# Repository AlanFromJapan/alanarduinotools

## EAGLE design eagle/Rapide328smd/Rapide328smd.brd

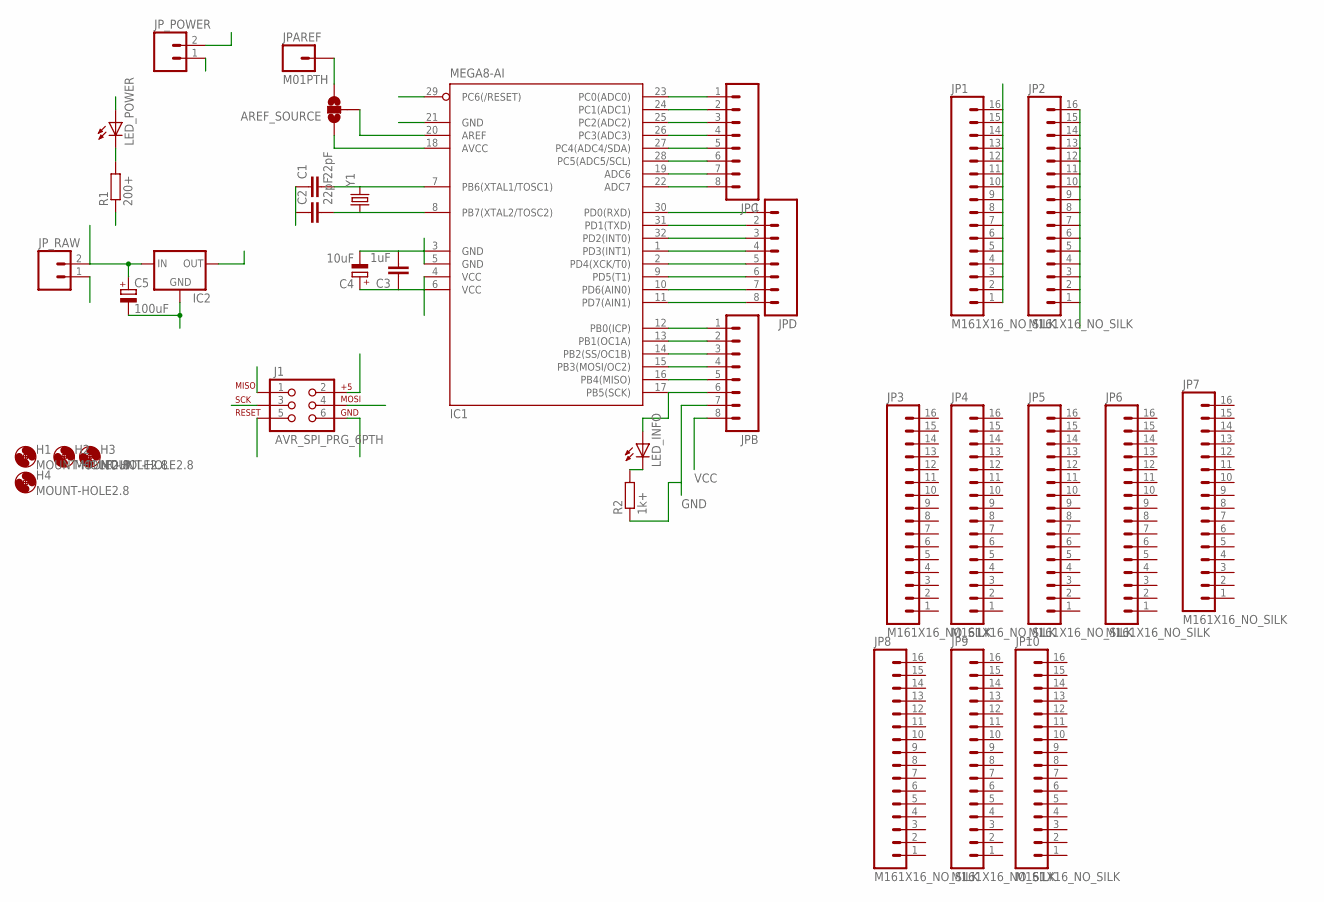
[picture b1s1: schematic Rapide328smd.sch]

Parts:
AREF_SOURCE: SOLDERJUMPER_2WAYPASTE1&2; SJ_3_PASTE1&2
C1, C2: 22pF; C025-024X044
C3: 1uF; C025-024X044
C4: 10uF; E2-5
C5: 100uF; E2-5
H1, H2, H3, H4: MOUNT-HOLE2.8; 2,8
IC1: MEGA8-AI; TQFP32-08
IC2: V_REG_78XXSINK; TO220-IGO
J1: AVR_SPI_PRG_6PTH; 2X3
JP1, JP2, JP3, JP4, JP5, JP6, JP7, JP8, JP9, JP10: M161X16_NO_SILK; 1X16_NO_SILK
JPAREF: M01PTH; 1X01
JPB: M081X08; 1X08
JPC: M081X08; 1X08
JPD: M081X08; 1X08
JP_POWER: M02PTH3; 1X02_LONGPADS
JP_RAW: M02PTH3; 1X02_LONGPADS
LED_INFO: LEDKA-3528ASYC; KA-3528ASYC
LED_POWER: LEDKA-3528ASYC; KA-3528ASYC
R1: 200+; 0204/7
R2: 1k+; 0204/5
Y1: CRYSTALHC49UV; HC49U-V

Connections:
GND: C1.1, C2.1, C3.2, C4.-, C5.-, IC1.3 (GND), IC1.5 (GND), IC1.21 (GND), IC2.GND, J1.6, JP2.1, JP2.2, JP2.3, JP2.4, JP2.5, JP2.6, JP2.7, JP2.8, JP2.9, JP2.10, JP2.11, JP2.12, JP2.13, JP2.14, JP2.15, JP2.16, JPB.7, JP_POWER.1, JP_RAW.1, R1.1, R2.1
MISO: IC1.16 (PB4(MISO)), J1.1, JPB.5
MOSI: IC1.15 (PB3(MOSI/OC2)), J1.4, JPB.4
unnamed: C1.2, IC1.7 (PB6(XTAL1/TOSC1)), Y1.2
unnamed: LED_INFO.C, R2.2
unnamed: IC1.25 (PC2(ADC2)), JPC.3
unnamed: IC1.24 (PC1(ADC1)), JPC.2
unnamed: IC1.23 (PC0(ADC0)), JPC.1
unnamed: IC1.22 (ADC7), JPC.8
unnamed: IC1.12 (PB0(ICP)), JPB.1
unnamed: IC1.19 (ADC6), JPC.7
unnamed: IC1.28 (PC5(ADC5/SCL)), JPC.6
unnamed: IC1.27 (PC4(ADC4/SDA)), JPC.5
unnamed: IC1.26 (PC3(ADC3)), JPC.4
unnamed: AREF_SOURCE.2, IC1.20 (AREF)
unnamed: C2.2, IC1.8 (PB7(XTAL2/TOSC2)), Y1.1
unnamed: AREF_SOURCE.3, JPAREF.1
unnamed: IC1.11 (PD7(AIN1)), JPD.8
unnamed: LED_POWER.C, R1.2
unnamed: IC1.10 (PD6(AIN0)), JPD.7
unnamed: IC1.13 (PB1(OC1A)), JPB.2
unnamed: IC1.9 (PD5(T1)), JPD.6
unnamed: IC1.14 (PB2(SS/OC1B)), JPB.3
unnamed: IC1.2 (PD4(XCK/T0)), JPD.5
unnamed: IC1.1 (PD3(INT1)), JPD.4
unnamed: IC1.32 (PD2(INT0)), JPD.3
unnamed: IC1.31 (PD1(TXD)), JPD.2
unnamed: IC1.30 (PD0(RXD)), JPD.1
RESET: IC1.29 (PC6(/RESET)), J1.5
SCK: IC1.17 (PB5(SCK)), J1.3, JPB.6, LED_INFO.A
VCC: AREF_SOURCE.1, C3.1, C4.+, IC1.4 (VCC), IC1.6 (VCC), IC1.18 (AVCC), IC2.OUT, J1.2, JP1.1, JP1.2, JP1.3, JP1.4, JP1.5, JP1.6, JP1.7, JP1.8, JP1.9, JP1.10, JP1.11, JP1.12, JP1.13, JP1.14, JP1.15, JP1.16, JPB.8, JP_POWER.2, LED_POWER.A
VRAW: C5.+, IC2.IN, JP_RAW.2

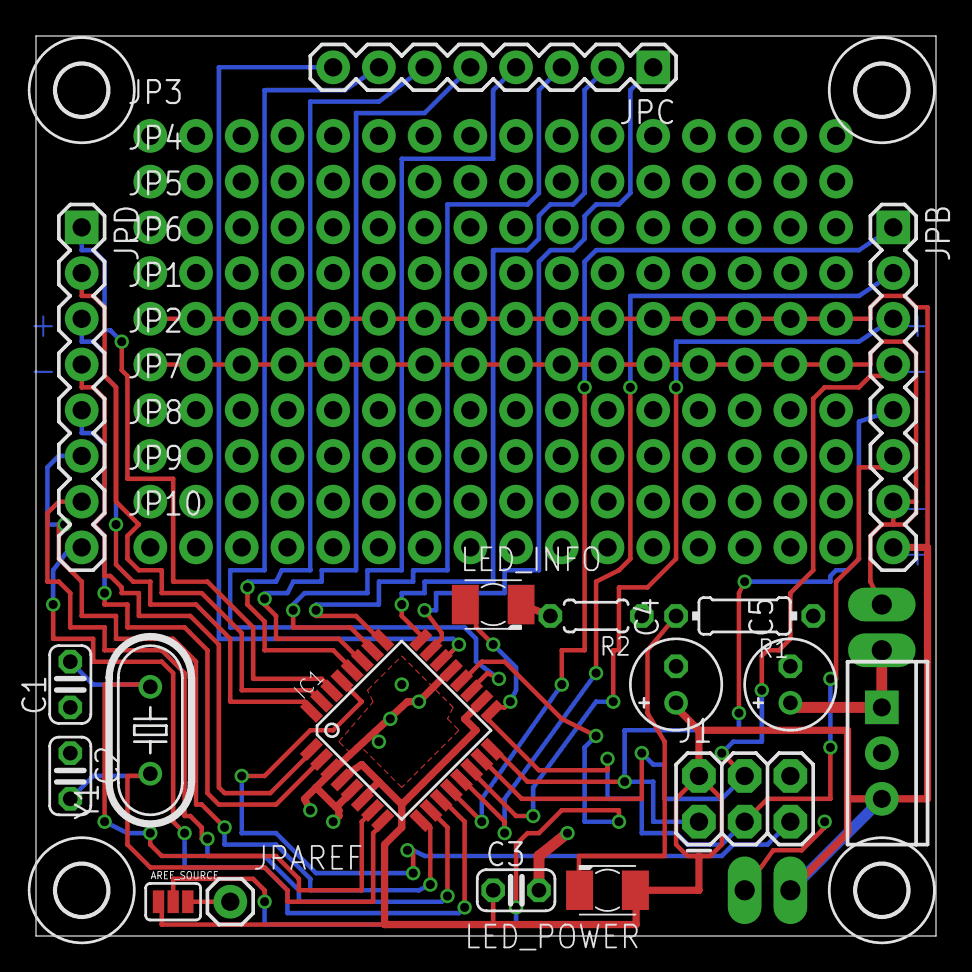
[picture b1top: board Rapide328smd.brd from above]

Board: 2 copper layers, 50.0 x 50.0 mm, 34 parts (0 on the bottom side), 32 nets.

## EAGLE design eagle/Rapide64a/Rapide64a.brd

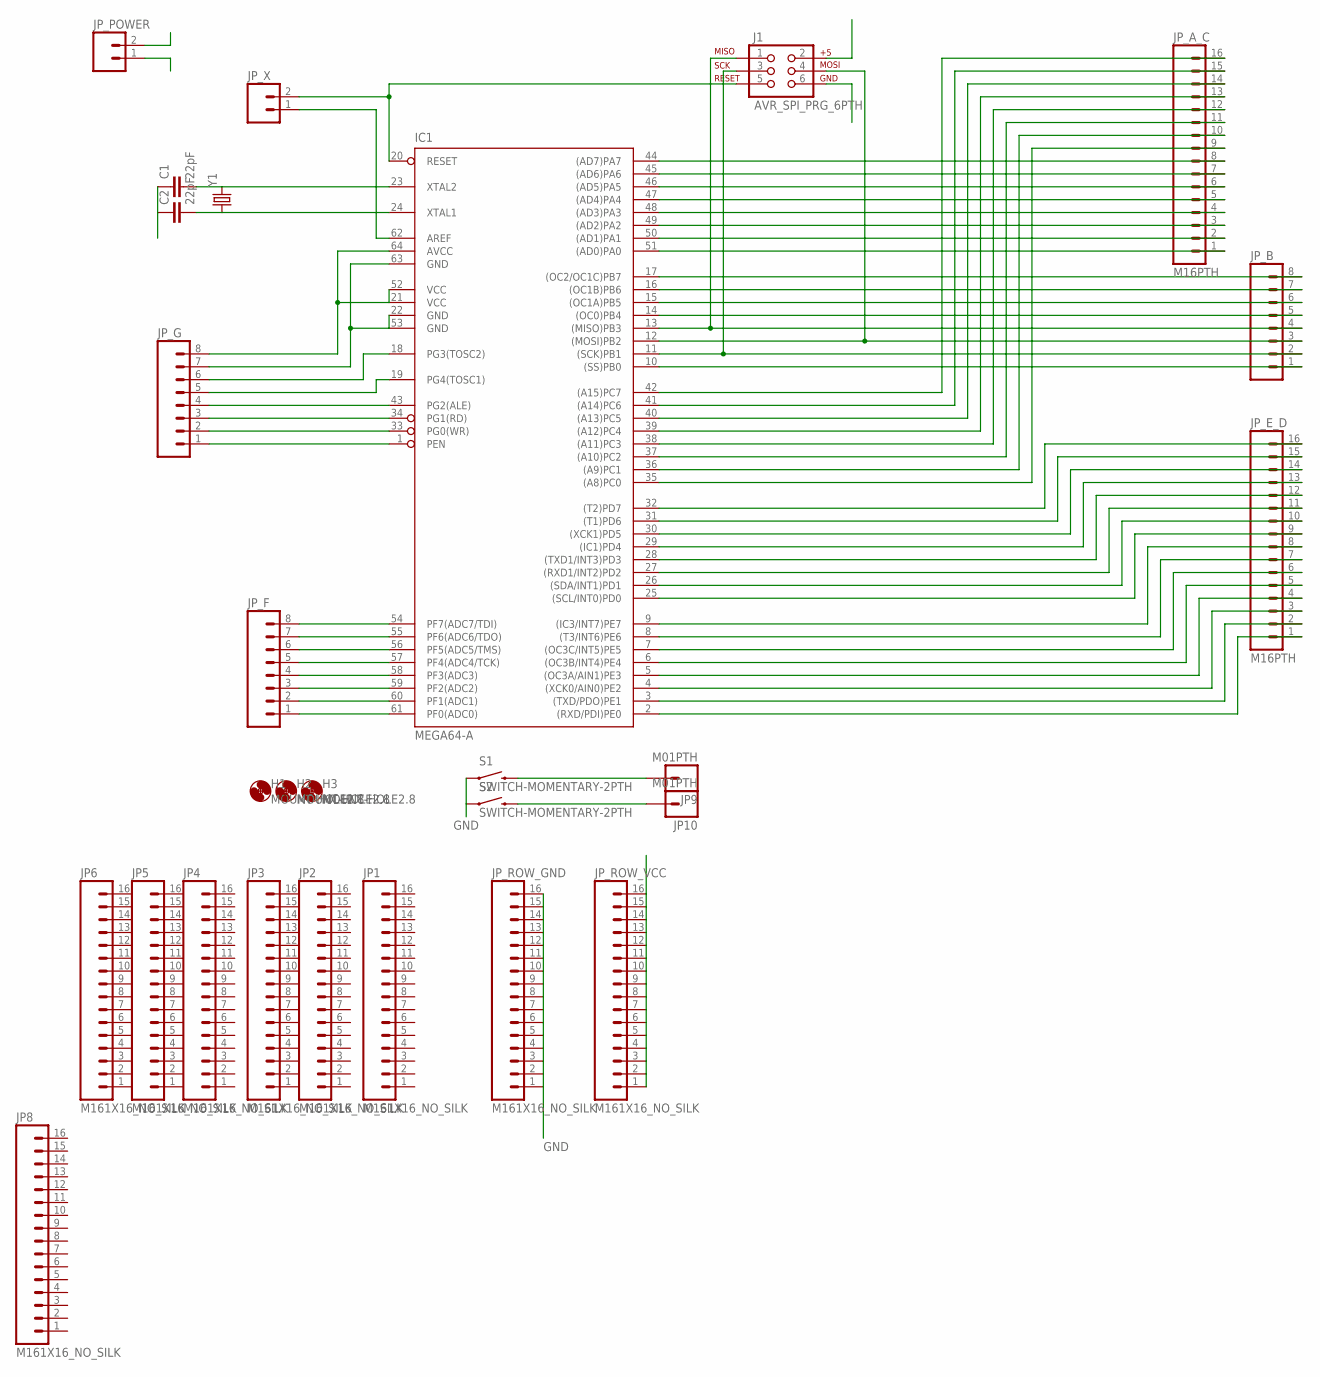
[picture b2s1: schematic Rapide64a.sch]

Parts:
C1, C2: 22pF; C025-024X044
H1, H2, H3: MOUNT-HOLE2.8; 2,8
IC1: MEGA64-A; TQFP64
J1: AVR_SPI_PRG_6PTH; 2X3
JP1, JP2, JP3, JP4, JP5, JP6, JP8: M161X16_NO_SILK; 1X16_NO_SILK
JP9, JP10: M01PTH; 1X01
JP_A_C: M16PTH; 1X16
JP_B: M081X08; 1X08
JP_E_D: M16PTH; 1X16
JP_F: M081X08; 1X08
JP_G: M081X08; 1X08
JP_POWER: M02PTH; 1X02
JP_ROW_GND: M161X16_NO_SILK; 1X16_NO_SILK
JP_ROW_VCC: M161X16_NO_SILK; 1X16_NO_SILK
JP_X: M02PTH; 1X02
S1, S2: SWITCH-MOMENTARY-2PTH; TACTILE-PTH
Y1: CRYSTALHC49UV; HC49U-V

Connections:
GND: C1.1, C2.1, IC1.22 (GND), IC1.53 (GND), IC1.63 (GND), J1.6, JP_G.7, JP_POWER.1, JP_ROW_GND.1, JP_ROW_GND.2, JP_ROW_GND.3, JP_ROW_GND.4, JP_ROW_GND.5, JP_ROW_GND.6, JP_ROW_GND.7, JP_ROW_GND.8, JP_ROW_GND.9, JP_ROW_GND.10, JP_ROW_GND.11, JP_ROW_GND.12, JP_ROW_GND.13, JP_ROW_GND.14, JP_ROW_GND.15, JP_ROW_GND.16, S1.1, S2.1
unnamed: IC1.6 ((OC3B/INT4)PE4), JP_E_D.5
unnamed: IC1.7 ((OC3C/INT5)PE5), JP_E_D.6
unnamed: IC1.8 ((T3/INT6)PE6), JP_E_D.7
unnamed: IC1.25 ((SCL/INT0)PD0), JP_E_D.9
unnamed: IC1.9 ((IC3/INT7)PE7), JP_E_D.8
unnamed: IC1.26 ((SDA/INT1)PD1), JP_E_D.10
unnamed: IC1.27 ((RXD1/INT2)PD2), JP_E_D.11
unnamed: IC1.58 (PF3(ADC3)), JP_F.4
unnamed: IC1.57 (PF4(ADC4/TCK)), JP_F.5
unnamed: IC1.56 (PF5(ADC5/TMS)), JP_F.6
unnamed: IC1.55 (PF6(ADC6/TDO)), JP_F.7
unnamed: IC1.54 (PF7(ADC7/TDI)), JP_F.8
unnamed: IC1.48 ((AD3)PA3), JP_A_C.4
unnamed: IC1.10 ((SS)PB0), JP_B.1
unnamed: IC1.49 ((AD2)PA2), JP_A_C.3
unnamed: IC1.17 ((OC2/OC1C)PB7), JP_B.8
unnamed: IC1.1 (PEN), JP_G.1
unnamed: IC1.33 (PG0(WR)), JP_G.2
unnamed: IC1.34 (PG1(RD)), JP_G.3
unnamed: IC1.18 (PG3(TOSC2)), JP_G.6
unnamed: IC1.19 (PG4(TOSC1)), JP_G.5
unnamed: IC1.39 ((A12)PC4), JP_A_C.13
unnamed: IC1.43 (PG2(ALE)), JP_G.4
unnamed: IC1.47 ((AD4)PA4), JP_A_C.5
unnamed: IC1.46 ((AD5)PA5), JP_A_C.6
unnamed: IC1.45 ((AD6)PA6), JP_A_C.7
unnamed: JP9.1, S1.3 (2)
unnamed: IC1.14 ((OC0)PB4), JP_B.5
unnamed: IC1.51 ((AD0)PA0), JP_A_C.1
unnamed: IC1.50 ((AD1)PA1), JP_A_C.2
unnamed: IC1.15 ((OC1A)PB5), JP_B.6
unnamed: JP10.1, S2.3 (2)
unnamed: IC1.44 ((AD7)PA7), JP_A_C.8
unnamed: IC1.16 ((OC1B)PB6), JP_B.7
unnamed: IC1.42 ((A15)PC7), JP_A_C.16
unnamed: IC1.41 ((A14)PC6), JP_A_C.15
unnamed: IC1.40 ((A13)PC5), JP_A_C.14
unnamed: IC1.35 ((A8)PC0), JP_A_C.9
unnamed: IC1.62 (AREF), JP_X.1
unnamed: C1.2, IC1.23 (XTAL2), Y1.2
unnamed: C2.2, IC1.24 (XTAL1), Y1.1
unnamed: IC1.4 ((XCK0/AIN0)PE2), JP_E_D.3
unnamed: IC1.5 ((OC3A/AIN1)PE3), JP_E_D.4
unnamed: IC1.28 ((TXD1/INT3)PD3), JP_E_D.12
unnamed: IC1.29 ((IC1)PD4), JP_E_D.13
unnamed: IC1.30 ((XCK1)PD5), JP_E_D.14
unnamed: IC1.31 ((T1)PD6), JP_E_D.15
unnamed: IC1.32 ((T2)PD7), JP_E_D.16
unnamed: IC1.38 ((A11)PC3), JP_A_C.12
unnamed: IC1.61 (PF0(ADC0)), JP_F.1
unnamed: IC1.60 (PF1(ADC1)), JP_F.2
unnamed: IC1.59 (PF2(ADC2)), JP_F.3
unnamed: IC1.37 ((A10)PC2), JP_A_C.11
unnamed: IC1.36 ((A9)PC1), JP_A_C.10
RESET: IC1.20 (RESET), J1.5, JP_X.2
SCK: IC1.11 ((SCK)PB1), J1.3, JP_B.2
VCC: IC1.21 (VCC), IC1.52 (VCC), IC1.64 (AVCC), J1.2, JP_G.8, JP_POWER.2, JP_ROW_VCC.1, JP_ROW_VCC.2, JP_ROW_VCC.3, JP_ROW_VCC.4, JP_ROW_VCC.5, JP_ROW_VCC.6, JP_ROW_VCC.7, JP_ROW_VCC.8, JP_ROW_VCC.9, JP_ROW_VCC.10, JP_ROW_VCC.11, JP_ROW_VCC.12, JP_ROW_VCC.13, JP_ROW_VCC.14, JP_ROW_VCC.15, JP_ROW_VCC.16

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
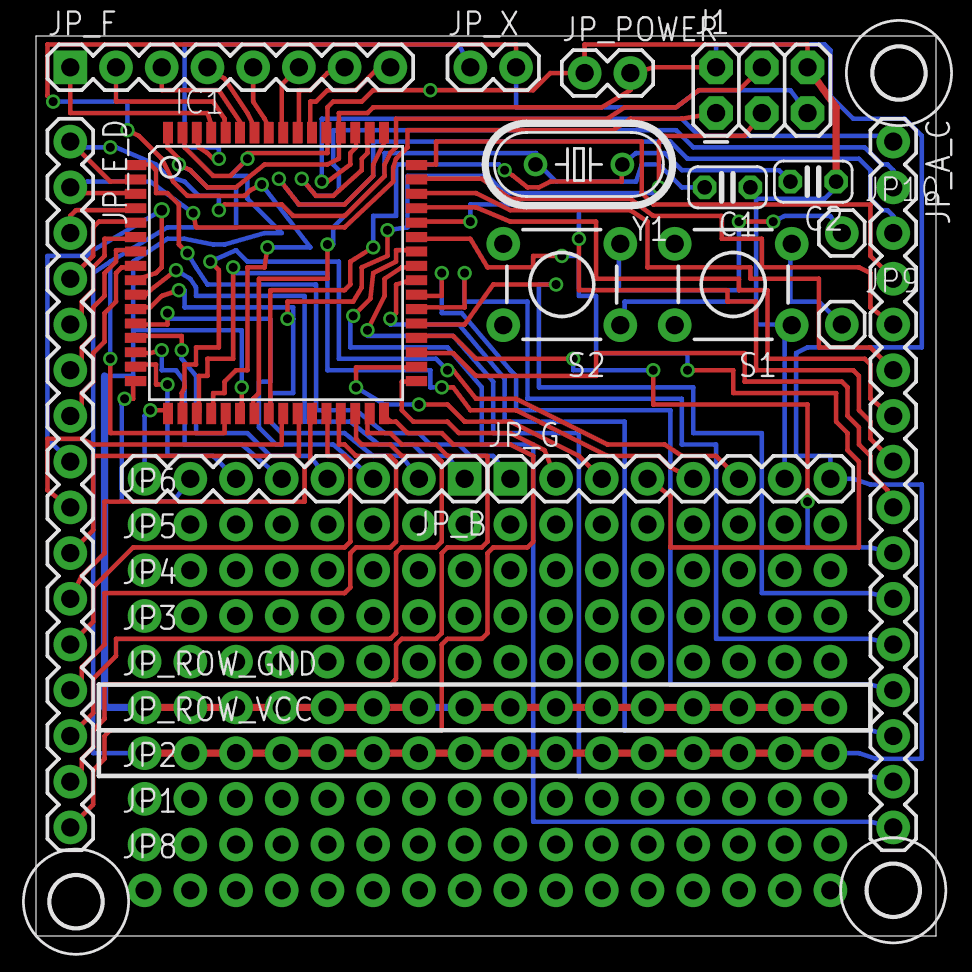
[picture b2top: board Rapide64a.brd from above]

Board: 2 copper layers, 50.0 x 50.0 mm, 28 parts (0 on the bottom side), 62 nets.

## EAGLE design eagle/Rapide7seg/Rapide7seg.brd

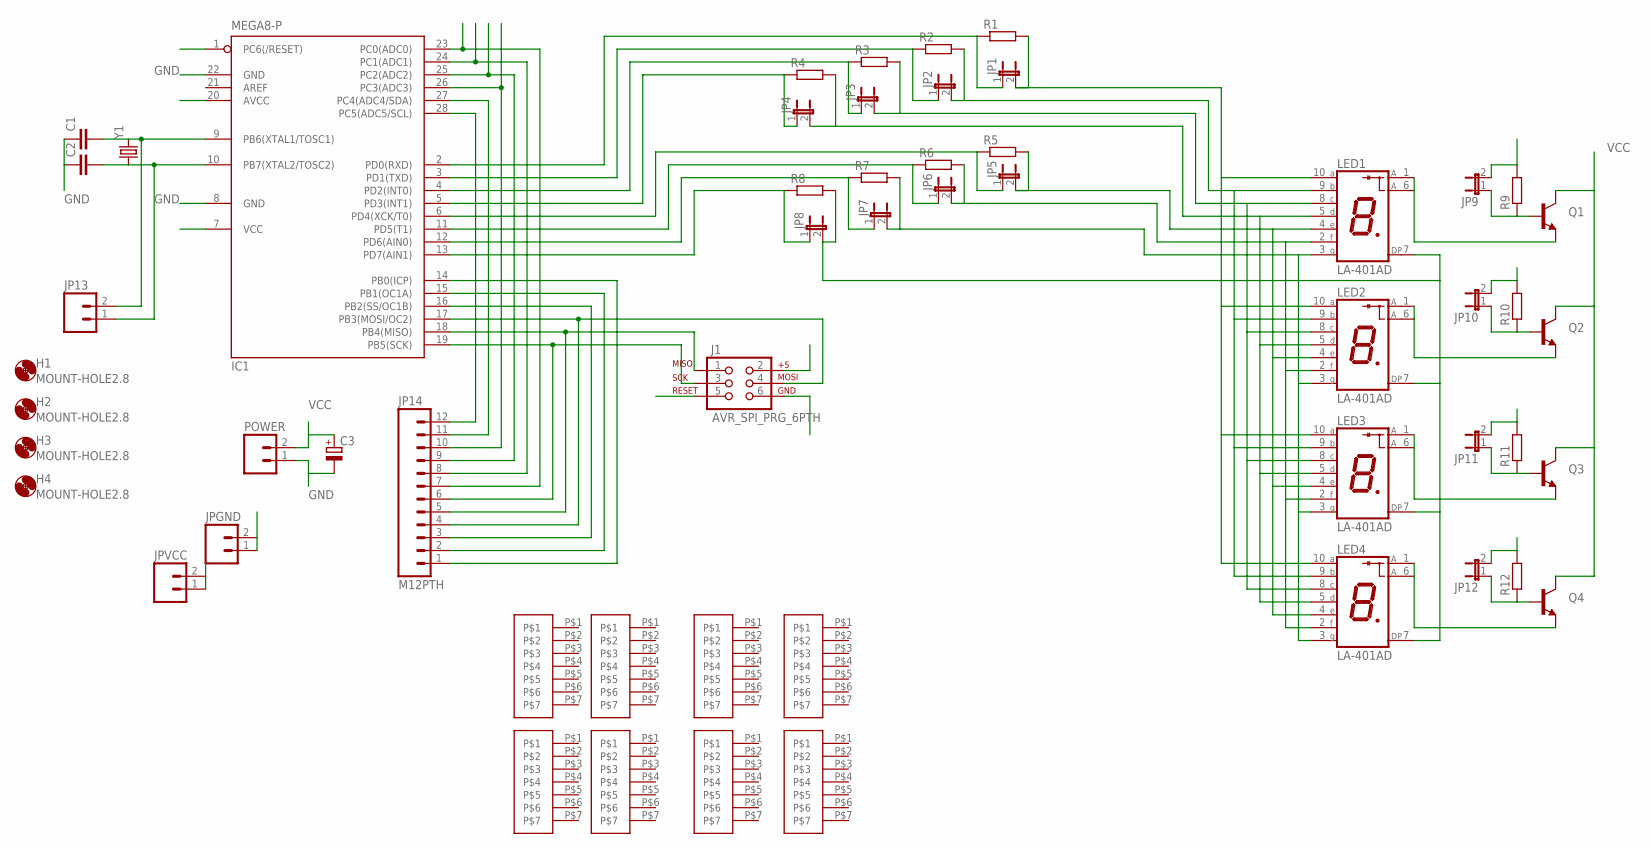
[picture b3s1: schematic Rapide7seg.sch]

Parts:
C1, C2: C-EU025-024X044; C025-024X044
C3: CPOL-EUE1.8-4; E1,8-4
H1, H2, H3, H4: MOUNT-HOLE2.8; 2,8
IC1: MEGA8-P; DIL28-3
J1: AVR_SPI_PRG_6PTH; 2X3
JP1, JP2, JP3, JP4, JP5, JP6, JP7, JP8, JP9, JP10, JP11, JP12: JUMPER-2SMD-NO; SJ_2S-NO
JP13: M02LOCK; 1X02_LOCK
JP14: M12PTH; 1X12
JPGND: M02PTH; 1X02
JPVCC: M02PTH; 1X02
LED1, LED2, LED3, LED4: LA-401AD; LA-401
POWER: M02LOCK_LONGPADS; 1X02_LOCK_LONGPADS
Q1, Q2, Q3, Q4: TRANSISTOR_NPNTO92; TO-92
R1, R2, R3, R4, R5, R6, R7, R8, R9, R10, R11, R12: R-EU_0204/7; 0204/7
U$1, U$2, U$3, U$4, U$5, U$6, U$7, U$8: M7_NOSILK
Y1: CRYSTALHC49UV; HC49U-V

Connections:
GND: C1.1, C2.1, C3.-, IC1.8 (GND), IC1.22 (GND), J1.6, JPGND.1, JPGND.2, POWER.1
L1: IC1.23 (PC0(ADC0)), JP9.2, JP14.7, R9.2
L2: IC1.24 (PC1(ADC1)), JP10.2, JP14.8, R10.2
L3: IC1.25 (PC2(ADC2)), JP11.2, JP14.9, R11.2
L4: IC1.26 (PC3(ADC3)), JP12.2, JP14.10, R12.2
unnamed: C1.2, IC1.9 (PB6(XTAL1/TOSC1)), JP13.2, Y1.2
unnamed: C2.2, IC1.10 (PB7(XTAL2/TOSC2)), JP13.1, Y1.1
unnamed: IC1.18 (PB4(MISO)), J1.1, JP14.5
unnamed: IC1.19 (PB5(SCK)), J1.3, JP14.6
unnamed: IC1.17 (PB3(MOSI/OC2)), J1.4, JP14.4
unnamed: JP12.1, Q4.2 (B), R12.1
unnamed: JP11.1, Q3.2 (B), R11.1
unnamed: JP10.1, Q2.2 (B), R10.1
unnamed: JP1.2, LED1.10 (A), LED2.10 (A), LED3.10 (A), LED4.10 (A), R1.2
unnamed: IC1.2 (PD0(RXD)), JP1.1, R1.1
unnamed: JP2.2, LED1.9 (B), LED2.9 (B), LED3.9 (B), LED4.9 (B), R2.2
unnamed: IC1.3 (PD1(TXD)), JP2.1, R2.1
unnamed: JP3.2, LED1.8 (C), LED2.8 (C), LED3.8 (C), LED4.8 (C), R3.2
unnamed: IC1.4 (PD2(INT0)), JP3.1, R3.1
unnamed: JP4.2, LED1.5 (D), LED2.5 (D), LED3.5 (D), LED4.5 (D), R4.2
unnamed: IC1.5 (PD3(INT1)), JP4.1, R4.1
unnamed: IC1.13 (PD7(AIN1)), JP8.1, R8.1
unnamed: JP8.2, LED1.7 (DP), LED2.7 (DP), LED3.7 (DP), LED4.7 (DP), R8.2
unnamed: IC1.12 (PD6(AIN0)), JP7.1, R7.1
unnamed: JP7.2, LED1.3 (G), LED2.3 (G), LED3.3 (G), LED4.3 (G), R7.2
unnamed: IC1.11 (PD5(T1)), JP6.1, R6.1
unnamed: JP6.2, LED1.2 (F), LED2.2 (F), LED3.2 (F), LED4.2 (F), R6.2
unnamed: IC1.6 (PD4(XCK/T0)), JP5.1, R5.1
unnamed: JP5.2, LED1.4 (E), LED2.4 (E), LED3.4 (E), LED4.4 (E), R5.2
unnamed: LED1.1 (A), LED1.6 (A), Q1.1 (E)
unnamed: LED2.1 (A), LED2.6 (A), Q2.1 (E)
unnamed: LED3.1 (A), LED3.6 (A), Q3.1 (E)
unnamed: LED4.1 (A), LED4.6 (A), Q4.1 (E)
unnamed: JP9.1, Q1.2 (B), R9.1
unnamed: IC1.28 (PC5(ADC5/SCL)), JP14.12
unnamed: IC1.27 (PC4(ADC4/SDA)), JP14.11
unnamed: IC1.16 (PB2(SS/OC1B)), JP14.3
unnamed: IC1.15 (PB1(OC1A)), JP14.2
unnamed: IC1.14 (PB0(ICP)), JP14.1
UCRESET: IC1.1 (PC6(/RESET)), J1.5
VCC: C3.+, IC1.7 (VCC), IC1.20 (AVCC), J1.2, JPVCC.1, POWER.2, Q1.3 (C), Q2.3 (C), Q3.3 (C), Q4.3 (C)

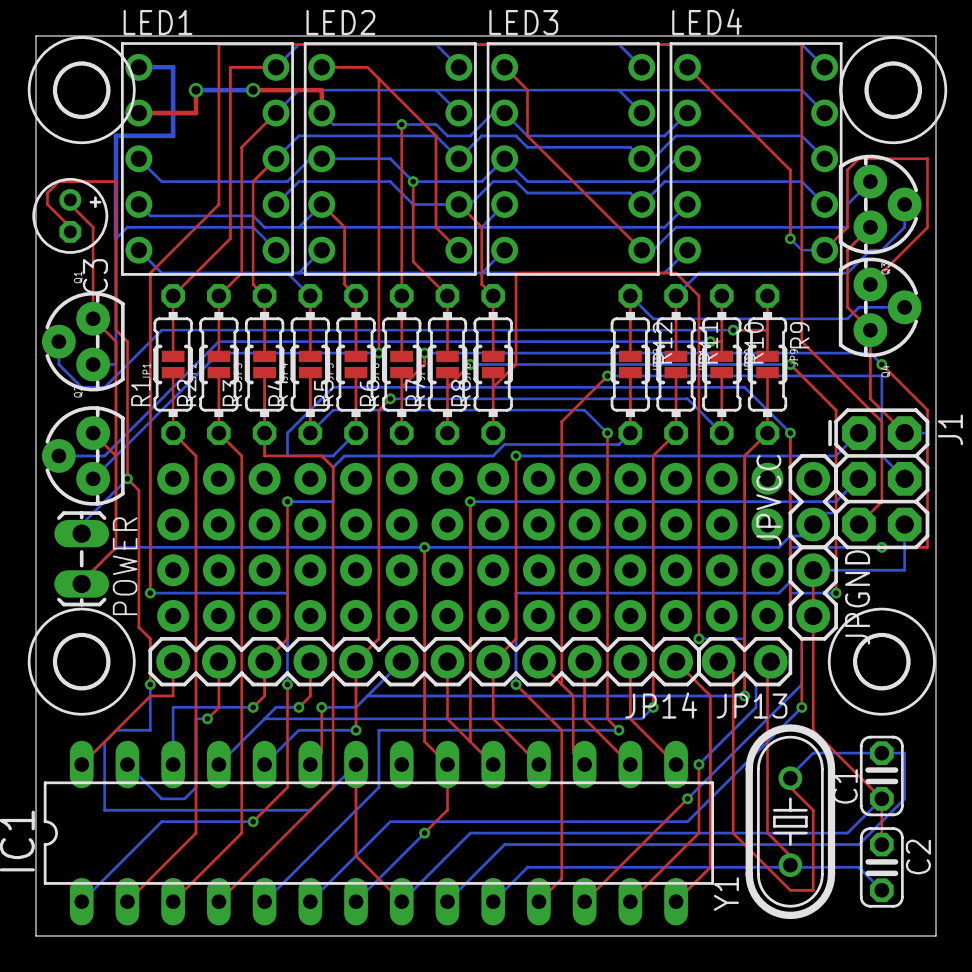
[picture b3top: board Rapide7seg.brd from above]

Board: 2 copper layers, 50.0 x 50.0 mm, 55 parts (0 on the bottom side), 41 nets.

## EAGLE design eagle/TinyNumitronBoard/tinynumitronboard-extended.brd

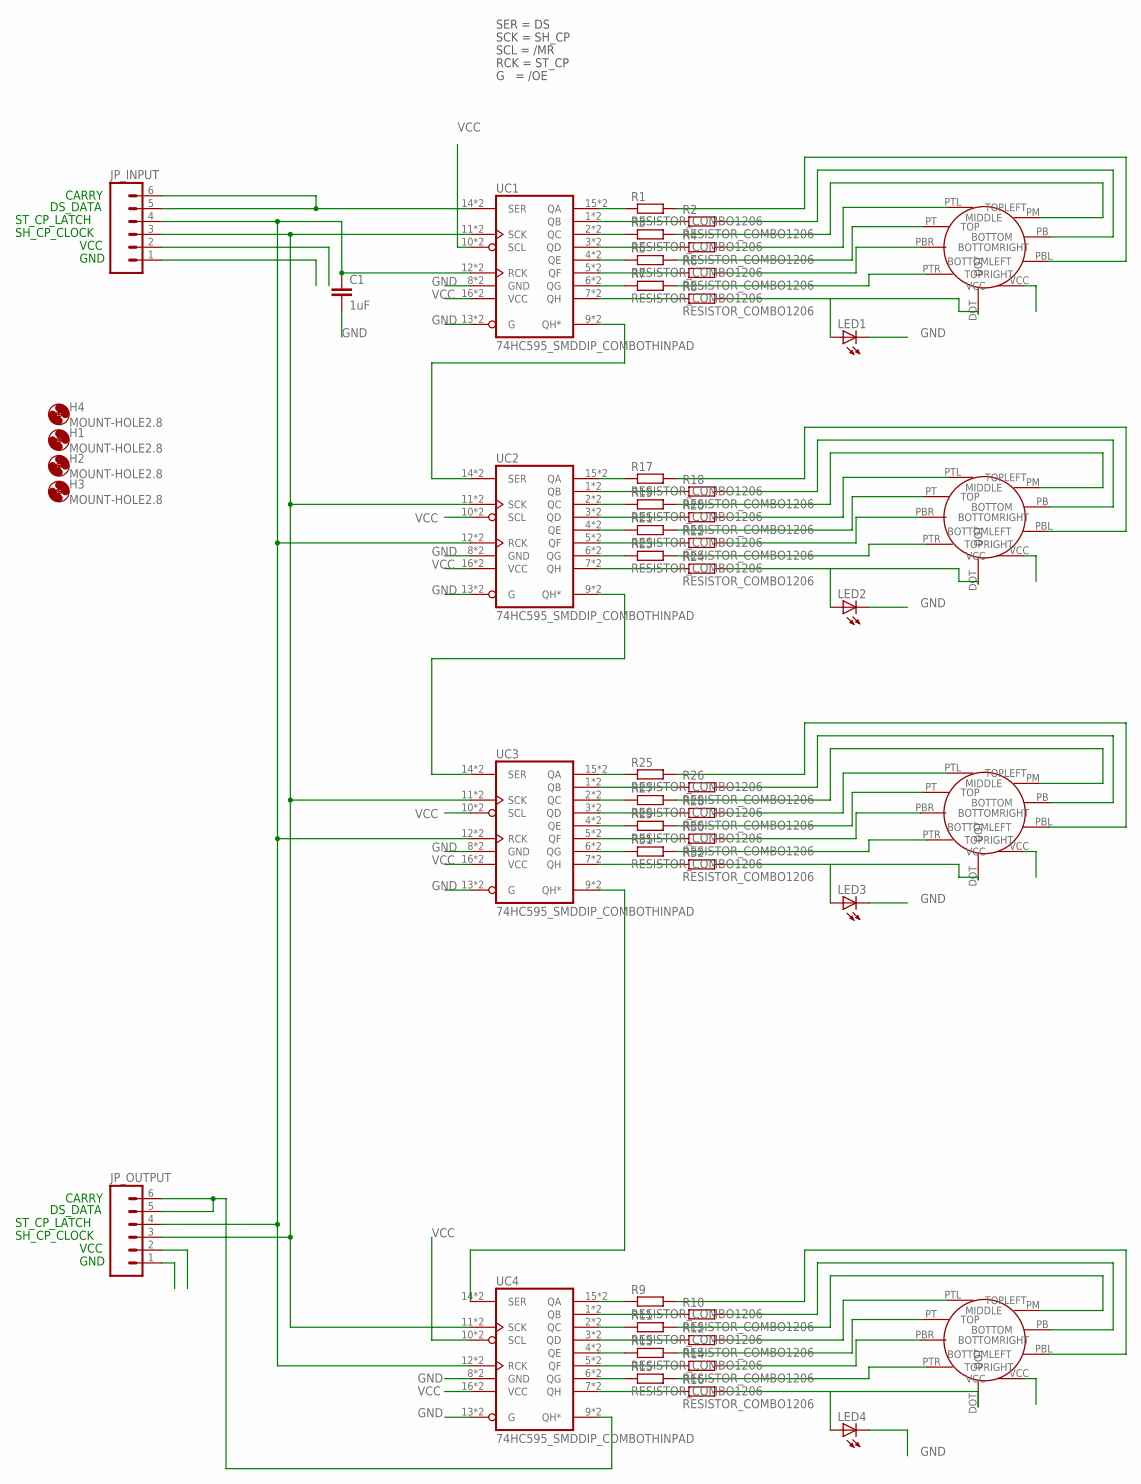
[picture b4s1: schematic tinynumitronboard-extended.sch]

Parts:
C1: 1uF; C050-024X044
H1, H2, H3, H4: MOUNT-HOLE2.8; 2,8
JP_INPUT: M06SIP; 1X06
JP_OUTPUT: M06SIP; 1X06
LED1, LED2, LED3, LED4: LEDKA-3528ASYC; KA-3528ASYC
R1, R2, R3, R4, R5, R6, R7, R8, R9, R10, R11, R12, R13, R14, R15, R16, R17, R18, R19, R20, R21, R22, R23, R24, R25, R26, R27, R28, R29, R30, R31, R32: RESISTOR_COMBO1206; 207-10_SMD_COMBO
U$1, U$2, U$5, U$7: IV16TINY_NUMITRON; IV16TINY_NUMITRON_PAC
UC1, UC2, UC3, UC4: 74HC595_SMDDIP_COMBOTHINPAD; DIL16_SO16_PAC2

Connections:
GND: C1.2, JP_INPUT.1, JP_OUTPUT.1, LED1.C, LED2.C, LED3.C, LED4.C, UC1.8 (GND), UC1.13 (G), UC1.S8 (GND), UC1.S13 (G), UC2.8 (GND), UC2.13 (G), UC2.S8 (GND), UC2.S13 (G), UC3.8 (GND), UC3.13 (G), UC3.S8 (GND), UC3.S13 (G), UC4.8 (GND), UC4.13 (G), UC4.S8 (GND), UC4.S13 (G)
unnamed: R1.2, R1.3 (2), U$1.PBL (BOTTOMLEFT)
unnamed: R2.2, R2.3 (2), U$1.PB (BOTTOM)
unnamed: R3.2, R3.3 (2), U$1.PM (MIDDLE)
unnamed: R4.2, R4.3 (2), U$1.PTL (TOPLEFT)
unnamed: R5.2, R5.3 (2), U$1.PT (TOP)
unnamed: R6.2, R6.3 (2), U$1.PBR (BOTTOMRIGHT)
unnamed: R7.2, R7.3 (2), U$1.PTR (TOPRIGHT)
unnamed: R1.1, R1.4 (1), UC1.15 (QA), UC1.S15 (QA)
unnamed: R2.1, R2.4 (1), UC1.1 (QB), UC1.S1 (QB)
unnamed: R3.1, R3.4 (1), UC1.2 (QC), UC1.S2 (QC)
unnamed: R4.1, R4.4 (1), UC1.3 (QD), UC1.S3 (QD)
unnamed: R5.1, R5.4 (1), UC1.4 (QE), UC1.S4 (QE)
unnamed: R6.1, R6.4 (1), UC1.5 (QF), UC1.S5 (QF)
unnamed: R7.1, R7.4 (1), UC1.6 (QG), UC1.S6 (QG)
unnamed: R8.1, R8.4 (1), UC1.7 (QH), UC1.S7 (QH)
unnamed: LED1.A, R8.2, R8.3 (2), U$1.DOT
unnamed: R9.2, R9.3 (2), U$2.PBL (BOTTOMLEFT)
unnamed: R10.2, R10.3 (2), U$2.PB (BOTTOM)
unnamed: JP_OUTPUT.5, JP_OUTPUT.6, UC4.9 (QH*), UC4.S9 (QH*)
unnamed: UC1.9 (QH*), UC1.S9 (QH*), UC2.14 (SER), UC2.S14 (SER)
unnamed: R11.2, R11.3 (2), U$2.PM (MIDDLE)
unnamed: R12.2, R12.3 (2), U$2.PTL (TOPLEFT)
unnamed: R13.2, R13.3 (2), U$2.PT (TOP)
unnamed: R14.2, R14.3 (2), U$2.PBR (BOTTOMRIGHT)
unnamed: R15.2, R15.3 (2), U$2.PTR (TOPRIGHT)
unnamed: R9.1, R9.4 (1), UC4.15 (QA), UC4.S15 (QA)
unnamed: R10.1, R10.4 (1), UC4.1 (QB), UC4.S1 (QB)
unnamed: R11.1, R11.4 (1), UC4.2 (QC), UC4.S2 (QC)
unnamed: R12.1, R12.4 (1), UC4.3 (QD), UC4.S3 (QD)
unnamed: R13.1, R13.4 (1), UC4.4 (QE), UC4.S4 (QE)
unnamed: R14.1, R14.4 (1), UC4.5 (QF), UC4.S5 (QF)
unnamed: R15.1, R15.4 (1), UC4.6 (QG), UC4.S6 (QG)
unnamed: R16.1, R16.4 (1), UC4.7 (QH), UC4.S7 (QH)
unnamed: LED4.A, R16.2, R16.3 (2), U$2.DOT
unnamed: R17.2, R17.3 (2), U$5.PBL (BOTTOMLEFT)
unnamed: R18.2, R18.3 (2), U$5.PB (BOTTOM)
unnamed: R19.2, R19.3 (2), U$5.PM (MIDDLE)
unnamed: R20.2, R20.3 (2), U$5.PTL (TOPLEFT)
unnamed: R21.2, R21.3 (2), U$5.PT (TOP)
unnamed: R22.2, R22.3 (2), U$5.PBR (BOTTOMRIGHT)
unnamed: R23.2, R23.3 (2), U$5.PTR (TOPRIGHT)
unnamed: R17.1, R17.4 (1), UC2.15 (QA), UC2.S15 (QA)
unnamed: R18.1, R18.4 (1), UC2.1 (QB), UC2.S1 (QB)
unnamed: R19.1, R19.4 (1), UC2.2 (QC), UC2.S2 (QC)
unnamed: R20.1, R20.4 (1), UC2.3 (QD), UC2.S3 (QD)
unnamed: R21.1, R21.4 (1), UC2.4 (QE), UC2.S4 (QE)
unnamed: R22.1, R22.4 (1), UC2.5 (QF), UC2.S5 (QF)
unnamed: R23.1, R23.4 (1), UC2.6 (QG), UC2.S6 (QG)
unnamed: R24.1, R24.4 (1), UC2.7 (QH), UC2.S7 (QH)
unnamed: LED2.A, R24.2, R24.3 (2), U$5.DOT
unnamed: UC2.9 (QH*), UC2.S9 (QH*), UC3.14 (SER), UC3.S14 (SER)
unnamed: R25.2, R25.3 (2), U$7.PBL (BOTTOMLEFT)
unnamed: R26.2, R26.3 (2), U$7.PB (BOTTOM)
unnamed: R27.2, R27.3 (2), U$7.PM (MIDDLE)
unnamed: R28.2, R28.3 (2), U$7.PTL (TOPLEFT)
unnamed: R29.2, R29.3 (2), U$7.PT (TOP)
unnamed: R30.2, R30.3 (2), U$7.PBR (BOTTOMRIGHT)
unnamed: R31.2, R31.3 (2), U$7.PTR (TOPRIGHT)
unnamed: R25.1, R25.4 (1), UC3.15 (QA), UC3.S15 (QA)
unnamed: R26.1, R26.4 (1), UC3.1 (QB), UC3.S1 (QB)
unnamed: R27.1, R27.4 (1), UC3.2 (QC), UC3.S2 (QC)
unnamed: R28.1, R28.4 (1), UC3.3 (QD), UC3.S3 (QD)
unnamed: R29.1, R29.4 (1), UC3.4 (QE), UC3.S4 (QE)
unnamed: R30.1, R30.4 (1), UC3.5 (QF), UC3.S5 (QF)
unnamed: R31.1, R31.4 (1), UC3.6 (QG), UC3.S6 (QG)
unnamed: R32.1, R32.4 (1), UC3.7 (QH), UC3.S7 (QH)
unnamed: LED3.A, R32.2, R32.3 (2), U$7.DOT
unnamed: UC3.9 (QH*), UC3.S9 (QH*), UC4.14 (SER), UC4.S14 (SER)
RCK: C1.1, JP_INPUT.4, JP_OUTPUT.4, UC1.12 (RCK), UC1.S12 (RCK), UC2.12 (RCK), UC2.S12 (RCK), UC3.12 (RCK), UC3.S12 (RCK), UC4.12 (RCK), UC4.S12 (RCK)
SCK: JP_INPUT.3, JP_OUTPUT.3, UC1.11 (SCK), UC1.S11 (SCK), UC2.11 (SCK), UC2.S11 (SCK), UC3.11 (SCK), UC3.S11 (SCK), UC4.11 (SCK), UC4.S11 (SCK)
SER: JP_INPUT.5, JP_INPUT.6, UC1.14 (SER), UC1.S14 (SER)
VCC: JP_INPUT.2, JP_OUTPUT.2, U$1.VCC, U$2.VCC, U$5.VCC, U$7.VCC, UC1.10 (SCL), UC1.16 (VCC), UC1.S10 (SCL), UC1.S16 (VCC), UC2.10 (SCL), UC2.16 (VCC), UC2.S10 (SCL), UC2.S16 (VCC), UC3.10 (SCL), UC3.16 (VCC), UC3.S10 (SCL), UC3.S16 (VCC), UC4.10 (SCL), UC4.16 (VCC), UC4.S10 (SCL), UC4.S16 (VCC)

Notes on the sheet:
SER = DS
SCK = SH_CP
SCL = /MR
RCK = ST_CP
G = /OE
GND
VCC
SH_CP_CLOCK
ST_CP_LATCH
DS_DATA
CARRY

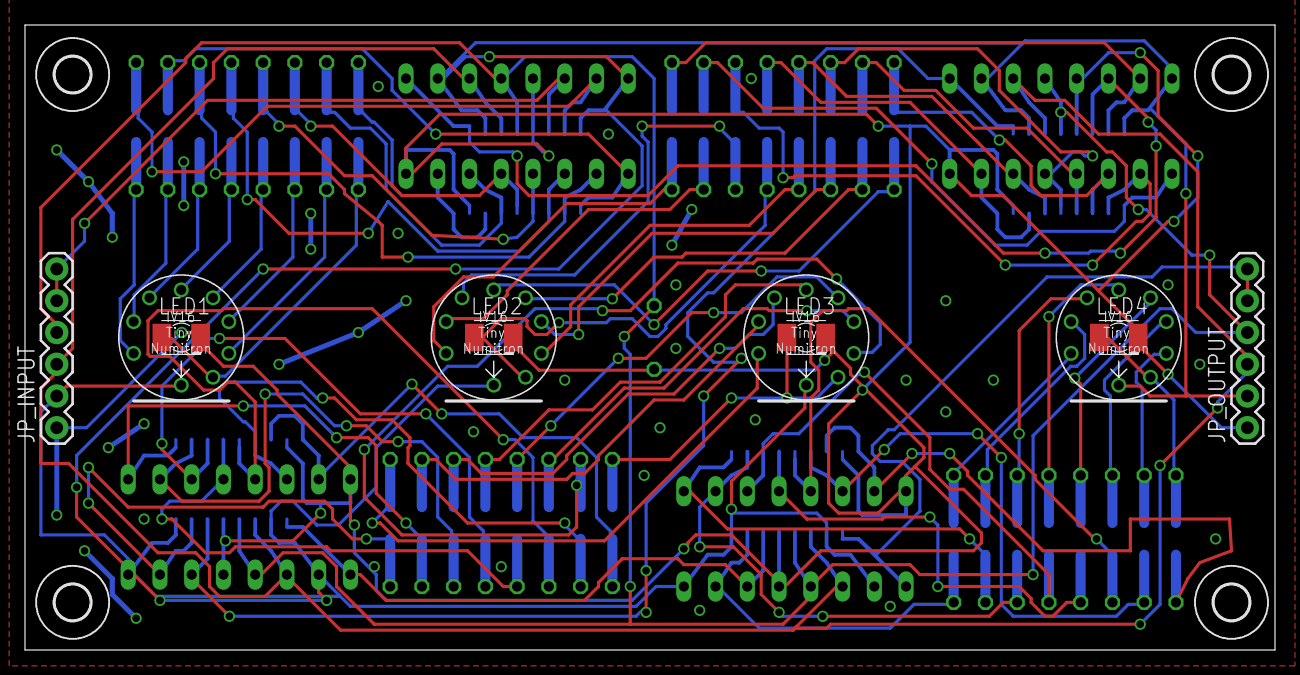
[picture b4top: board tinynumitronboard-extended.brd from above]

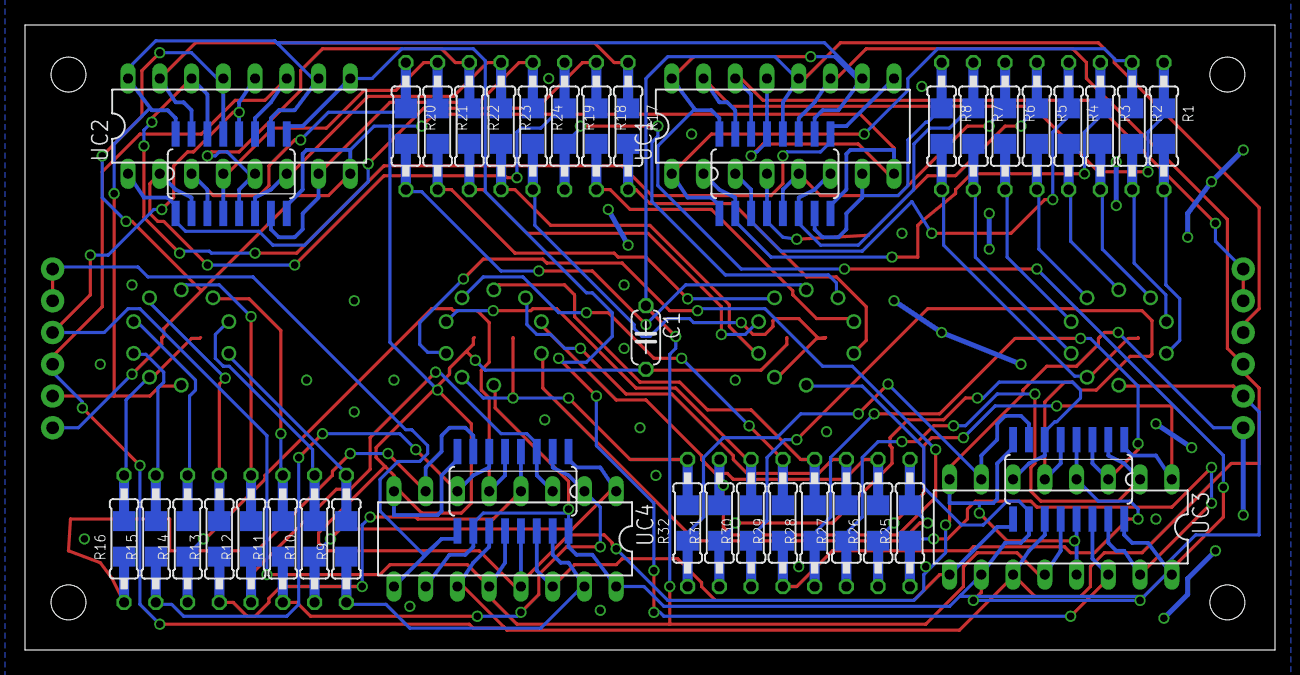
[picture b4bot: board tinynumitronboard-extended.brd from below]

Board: 4 copper layers, 100.0 x 50.0 mm, 52 parts (37 on the bottom side), 73 nets.

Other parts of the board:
U$3: GEARS_1000X500

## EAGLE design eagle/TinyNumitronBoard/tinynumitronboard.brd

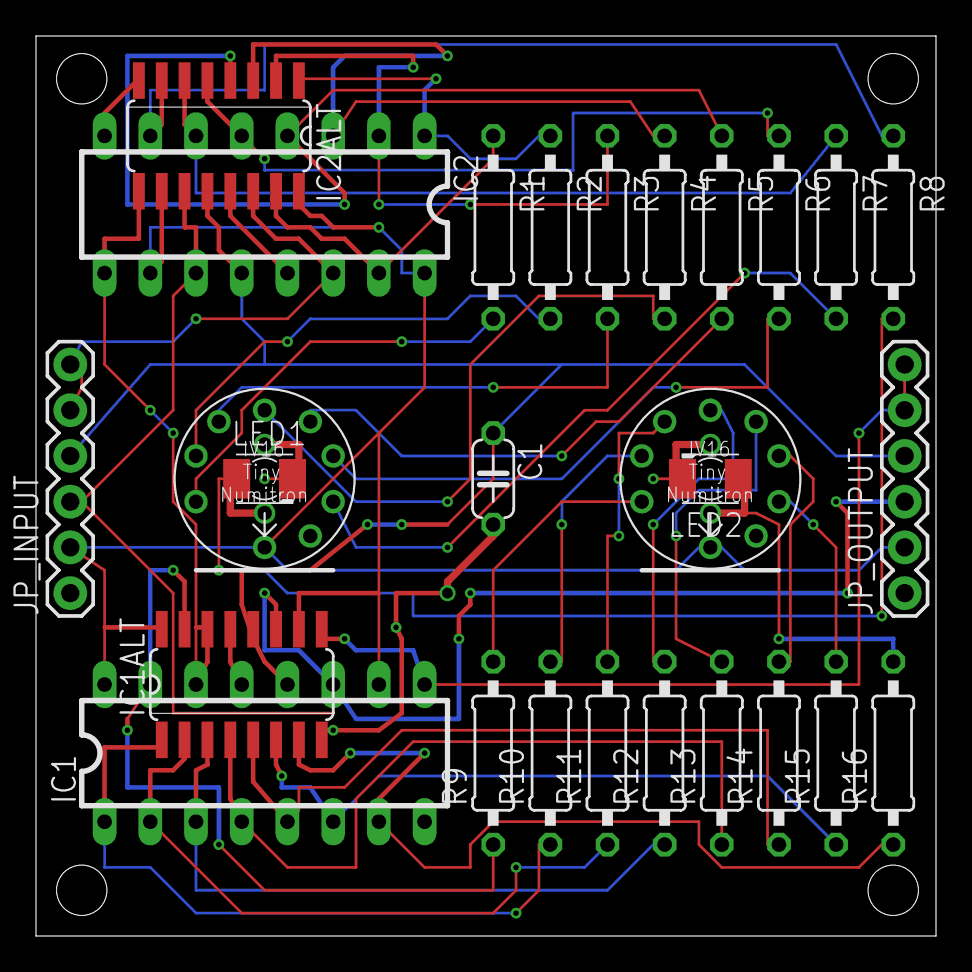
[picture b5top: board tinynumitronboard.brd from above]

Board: 2 copper layers, 50.0 x 50.0 mm, 27 parts (0 on the bottom side), 39 nets.

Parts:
C1: 1uF; C050-024X044
IC1, IC2: 74LS595N; DIL16
IC1ALT, IC2ALT: 74HCT595D; SO16
JP_INPUT: 1X06
JP_OUTPUT: 1X06
LED1, LED2: KA-3528ASYC
R1, R2, R3, R4, R5, R6, R7, R8, R9, R10, R11, R12, R13, R14, R15, R16: 0207/10
U$1, U$2: IV16TINY_NUMITRON; IV16TINY_NUMITRON_PAC

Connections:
GND: C1.2, IC1.8, IC1.13, IC1ALT.8, IC1ALT.13, IC2.8, IC2.13, IC2ALT.8, IC2ALT.13, JP_INPUT.1, JP_OUTPUT.1, LED1.C, LED2.C
unnamed: R1.2, U$1.PBL
unnamed: R2.2, U$1.PB
unnamed: R3.2, U$1.PM
unnamed: R4.2, U$1.PTL
unnamed: R5.2, U$1.PT
unnamed: R6.2, U$1.PBR
unnamed: R7.2, U$1.PTR
unnamed: IC1.1, IC1ALT.1, R10.1
unnamed: IC1.2, IC1ALT.2, R11.1
unnamed: IC1.3, IC1ALT.3, R12.1
unnamed: IC1.4, IC1ALT.4, R13.1
unnamed: IC2.4, IC2ALT.4, R5.1
unnamed: IC2.3, IC2ALT.3, R4.1
unnamed: IC1.5, IC1ALT.5, R14.1
unnamed: IC1.6, IC1ALT.6, R15.1
unnamed: IC2.7, IC2ALT.7, R8.1
unnamed: LED1.A, R8.2
unnamed: IC2.2, IC2ALT.2, R3.1
unnamed: R9.2, U$2.PBL
unnamed: R10.2, U$2.PB
unnamed: IC1.7, IC1ALT.7, R16.1
unnamed: IC1.14, IC1ALT.14, IC2.9, IC2ALT.9
unnamed: R11.2, U$2.PM
unnamed: R12.2, U$2.PTL
unnamed: R13.2, U$2.PT
unnamed: R14.2, U$2.PBR
unnamed: R15.2, U$2.PTR
unnamed: LED2.A, R16.2
unnamed: IC2.14, IC2ALT.14, JP_INPUT.5, JP_INPUT.6
unnamed: IC2.1, IC2ALT.1, R2.1
unnamed: IC2.15, IC2ALT.15, R1.1
unnamed: IC2.6, IC2ALT.6, R7.1
unnamed: IC2.5, IC2ALT.5, R6.1
unnamed: C1.1, IC1.12, IC1ALT.12, IC2.12, IC2ALT.12, JP_INPUT.4, JP_OUTPUT.4
unnamed: IC1.15, IC1ALT.15, R9.1
unnamed: IC1.11, IC1ALT.11, IC2.11, IC2ALT.11, JP_INPUT.3, JP_OUTPUT.3
unnamed: IC1.9, IC1ALT.9, JP_OUTPUT.5, JP_OUTPUT.6
VCC: IC1.10, IC1.16, IC1ALT.10, IC1ALT.16, IC2.10, IC2.16, IC2ALT.10, IC2ALT.16, JP_INPUT.2, JP_OUTPUT.2, U$1.VCC, U$2.VCC

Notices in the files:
parts and their libraries:
SparkFun-Connectors: Licensing: CC v3.0 Share-Alike You are welcome to use this library for commercial purposes.
